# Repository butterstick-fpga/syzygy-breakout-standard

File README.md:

# SYZYGY breakout

SYZYGY is an FPGA expansion standard for medium to high speed interfaces. Learn more and check out the specifications here: [https://syzygyfpga.io/](https://syzygyfpga.io/)

> Note that the attiny44A populated on boards from the GroupGets campaign are delivered blank.

---

## What is it

- A breakout with all 32 I/O pins broken out to a 0.1" header. 
- A small prototyping area is also provided.
- attiny44a provided to enable SYZYGY DNA features.

## Photos

## Prototyping area

The prototyping area is set up like a traditional breadboard layout, if you examine the back of the board you can see tracks that run between the 0.1" prototyping holes.
You can also see these details in the KiCad design files.

Available on the back of the board is various power rails that are available to "jumper" across to the prototyping area.

## Attiny44A Firmware

The attiny44A is fitted to provide SYZYGY DNA features, a mechanism that SYZYGY controllers can poll to determine what pods are connected, and their VCCIO range etc.

Currently, the firmware for this hasn't been developed/tested yet. This feature also requires the controller (E.g. ButterStick) to have a mechanism to poll the pods for this info.

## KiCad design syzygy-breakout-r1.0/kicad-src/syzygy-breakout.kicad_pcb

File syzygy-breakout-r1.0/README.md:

# SYZYGY breakout

SYZYGY is an FPGA expansion standard for medium to high speed interfaces. Learn more and check out the specifications here: [https://syzygyfpga.io/](https://syzygyfpga.io/)

---

## What is it

A breakout with all 32 I/O pins broken out to a 0.1" header. 

A small prototyping area is also provided.

## Folder structure

```
kicad-src: KiCad v6 source files
production:
 - Gerbers:      [project]_gerbers.zip
 - Schematic:    [project].pdf
 - Board render: [project].png
```

## Photos

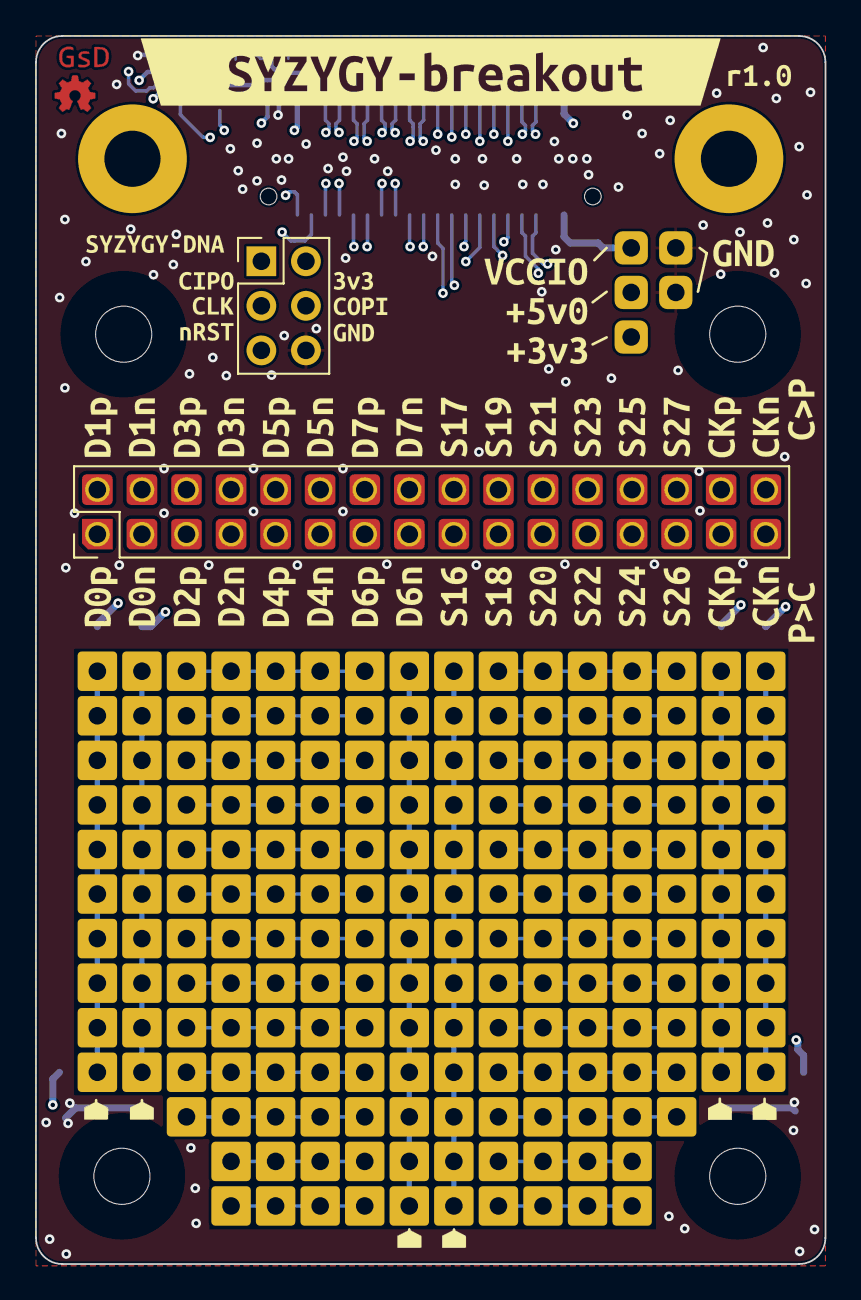
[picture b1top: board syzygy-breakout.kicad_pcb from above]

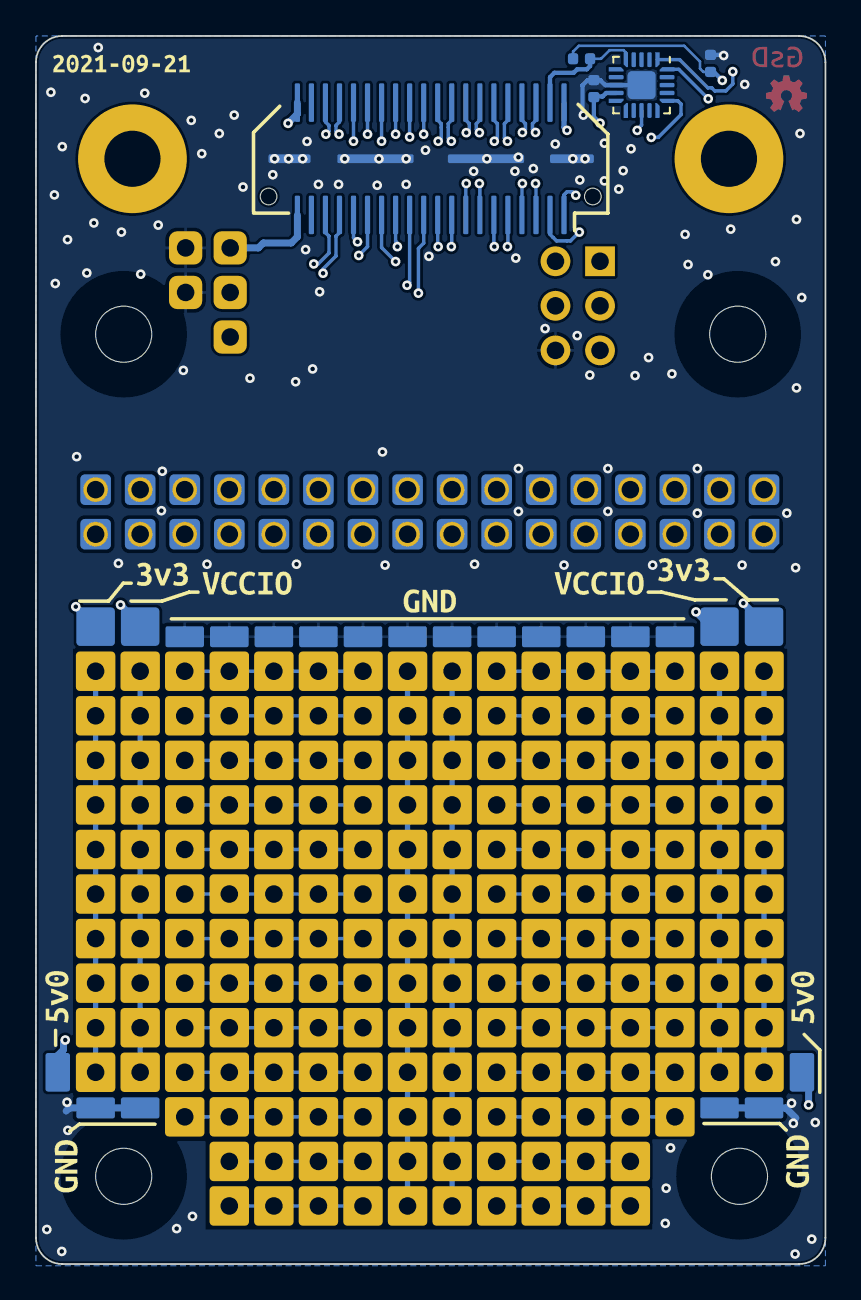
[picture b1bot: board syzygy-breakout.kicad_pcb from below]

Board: 4 copper layers, 45.0 x 70.0 mm, 73 parts (15 on the bottom side), 41 nets.

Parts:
C9: 0.1uF; C_0402_1005Metric
C10: 1uF; C_0402_1005Metric
H1, H2, H3, H4: MountingHole; MountingHole_3.2mm_M3_DIN965
J1: SYZYGY-STD; SYZYGY-STD-POD
J2: Conn_02x16_Odd_Even; PinHeader_2x16_P2.54mm_Vertical
J3: TagConnect; PinHeader_2x03_P2.54mm_Vertical
J4, J4#2, J5, J6, J6#2: Conn_01x01_Male; PinHeader_1x01_P2.54mm_Vertical
R15: 10K; R_0402_1005Metric
U2: ATtiny44A-MMH; QFN-20-1EP_3x3mm_P0.45mm_EP1.6x1.6mm
kibuzzard-61491A46, kibuzzard-61491A46#2: G***; kibuzzard-61491A46
kibuzzard-61491AB0, kibuzzard-61491AB0#2: G***; kibuzzard-61491AB0
kibuzzard-61491ABE, kibuzzard-61491ABE#2: G***; kibuzzard-61491ABE
kibuzzard-61491FCC: G***; kibuzzard-61491FCC
kibuzzard-61492D1E: G***; kibuzzard-61492D1E
kibuzzard-61492D2E: G***; kibuzzard-61492D2E
kibuzzard-61492D9C: G***; kibuzzard-61492D9C
kibuzzard-61492D24: G***; kibuzzard-61492D24
kibuzzard-614919EA, kibuzzard-614919EA#2, kibuzzard-614919EA#3: G***; kibuzzard-614919EA
kibuzzard-614928B5: G***; kibuzzard-614928B5
kibuzzard-614928DD: G***; kibuzzard-614928DD
kibuzzard-614928EC: G***; kibuzzard-614928EC
kibuzzard-614928F9: G***; kibuzzard-614928F9
kibuzzard-614937C5: G***; kibuzzard-614937C5
kibuzzard-614937CF: G***; kibuzzard-614937CF
kibuzzard-614937D4: G***; kibuzzard-614937D4
kibuzzard-614937D9: G***; kibuzzard-614937D9
kibuzzard-614937DF: G***; kibuzzard-614937DF
kibuzzard-614937E3: G***; kibuzzard-614937E3
kibuzzard-614937E9: G***; kibuzzard-614937E9
kibuzzard-614937EE: G***; kibuzzard-614937EE
kibuzzard-614937F3: G***; kibuzzard-614937F3
kibuzzard-614937F8: G***; kibuzzard-614937F8
kibuzzard-614937FC: G***; kibuzzard-614937FC
kibuzzard-6149253E: G***; kibuzzard-6149253E
kibuzzard-6149290C: G***; kibuzzard-6149290C
kibuzzard-6149371A: G***; kibuzzard-6149371A
kibuzzard-6149372C: G***; kibuzzard-6149372C
kibuzzard-6149373C: G***; kibuzzard-6149373C
kibuzzard-6149374B: G***; kibuzzard-6149374B
kibuzzard-6149374F: G***; kibuzzard-6149374F
kibuzzard-6149375A: G***; kibuzzard-6149375A
kibuzzard-6149375F: G***; kibuzzard-6149375F
kibuzzard-6149380F, kibuzzard-6149380F#2: G***; kibuzzard-6149380F
kibuzzard-6149386B: G***; kibuzzard-6149386B
kibuzzard-61492572: G***; kibuzzard-61492572
kibuzzard-61492903: G***; kibuzzard-61492903
kibuzzard-61492915: G***; kibuzzard-61492915
kibuzzard-61493714: G***; kibuzzard-61493714
kibuzzard-61493721: G***; kibuzzard-61493721
kibuzzard-61493726: G***; kibuzzard-61493726
kibuzzard-61493731: G***; kibuzzard-61493731
kibuzzard-61493737: G***; kibuzzard-61493737
kibuzzard-61493742: G***; kibuzzard-61493742
kibuzzard-61493746: G***; kibuzzard-61493746
kibuzzard-61493754: G***; kibuzzard-61493754
kibuzzard-61493763: G***; kibuzzard-61493763
kibuzzard-61493801: G***; kibuzzard-61493801
kibuzzard-61493817, kibuzzard-61493817#2: G***; kibuzzard-61493817
kibuzzard-61493858: G***; kibuzzard-61493858

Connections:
+3V3: C9.1, C10.1, J1.40 (+3.3V), J3.2, J5.1, R15.1, U2.9 (VCC)
+5V: J1.2 (+5V), J4#2.1
/C2P_CLK_N: J1.36 (C2P_CLKN), J2.32
/C2P_CLK_P: J1.34 (C2P_CLKP), J2.30
/D0_N: J1.7 (S2_D0N), J2.3
/D0_P: J1.5 (S0_D0P), J2.1
/D1_N: J1.8 (S3_D1N), J2.4
/D1_P: J1.6 (S1_D1P), J2.2
/D2_N: J1.11 (S6_D2N), J2.7
/D2_P: J1.9 (S4_D2P), J2.5
/D3_N: J1.12 (S7_D3N), J2.8
/D3_P: J1.10 (S5_D3P), J2.6
/D4_N: J1.15 (S10_D4N), J2.11
/D4_P: J1.13 (S8_D4P), J2.9
/D5_N: J1.16 (S11_D5N), J2.12
/D5_P: J1.14 (S9_D5P), J2.10
/D6_N: J1.19 (S14_D6N), J2.15
/D6_P: J1.17 (S12_D6P), J2.13
/D7_N: J1.20 (S15_D7N), J2.16
/D7_P: J1.18 (S13_D7P), J2.14
/P2C_CLK_N: J1.35 (P2C_CLKN), J2.31
/P2C_CLK_P: J1.33 (P2C_CLKP), J2.29
/Peripheral MCU/MISO: J3.1, U2.20 (PA5)
/Peripheral MCU/~RESET: J3.5, U2.13 (~RESET~/PB3)
/RGA: J1.4 (R_GA), R15.2, U2.5 (AREF/PA0)
/S16: J1.21 (S16), J2.17
/S17: J1.22 (S17), J2.18
/S18: J1.23 (S18), J2.19
/S19: J1.24 (S19), J2.20
/S20: J1.25 (S20), J2.21
/S21: J1.26 (S21), J2.22
/S22: J1.27 (S22), J2.23
/S23: J1.28 (S23), J2.24
/S24: J1.29 (S24), J2.25
/S25: J1.30 (S25), J2.26
/S26: J1.31 (S26), J2.27
/S27: J1.32 (S27), J2.28
/SCL: J1.1 (SCL), J3.3, U2.1 (PA4)
/SDA: J1.3 (SDA), J3.4, U2.16 (PA6)
/VCCIO: J1.39 (VIO1), J6.1
GND: C9.2, C10.2, J1.41 (GND), J3.6, J4.1, J6#2.1, U2.8 (GND), U2.21 (GND)

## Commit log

2021-12-02 Update README
    - Add photos
2021-12-12 Add datasheet
2021-12-12 Add high-res product images
